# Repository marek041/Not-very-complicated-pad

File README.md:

# Not-very-complicated-pad
simple macro pad. 6 keys with oled display and Xiao RP2040. Macro pad for simple tasks like ctrl+c, ctrl+v, etc. also programs opening with windows search and shutdown button :O

## Features: 
- 6 keys
- 128x32 oled display
- 3 leds
- pretty silkcreen art
- cool case :)

## Cad design:
  This includes 3d printed case of 3 parts, everything is connected with M3 bolts screwed in plastic.
  
  It was made in Fusion360 and components imported from KiCad
  (i added step files so it could generate full PCB with components )

  it is all in cad folder

## PCB:
PCB i made in KiCad 

and Schematic 

## BOM:
  All components right there:

   - 6x Cheery MX switches
   - 6x DSA keycaps
   - 4x M3x16mm SHCS bolts
   - 6x 1N4148 DO-35 diodes
   - 3x WS28128 LEDs
   - 1x 0.91" 128x32 OLED Display
   - 1x XIAO RP2040
   - Case (3 printed parts)
 
## EXTRA stuff
This is my first project on Hack Club and also first time designing PCB
:D

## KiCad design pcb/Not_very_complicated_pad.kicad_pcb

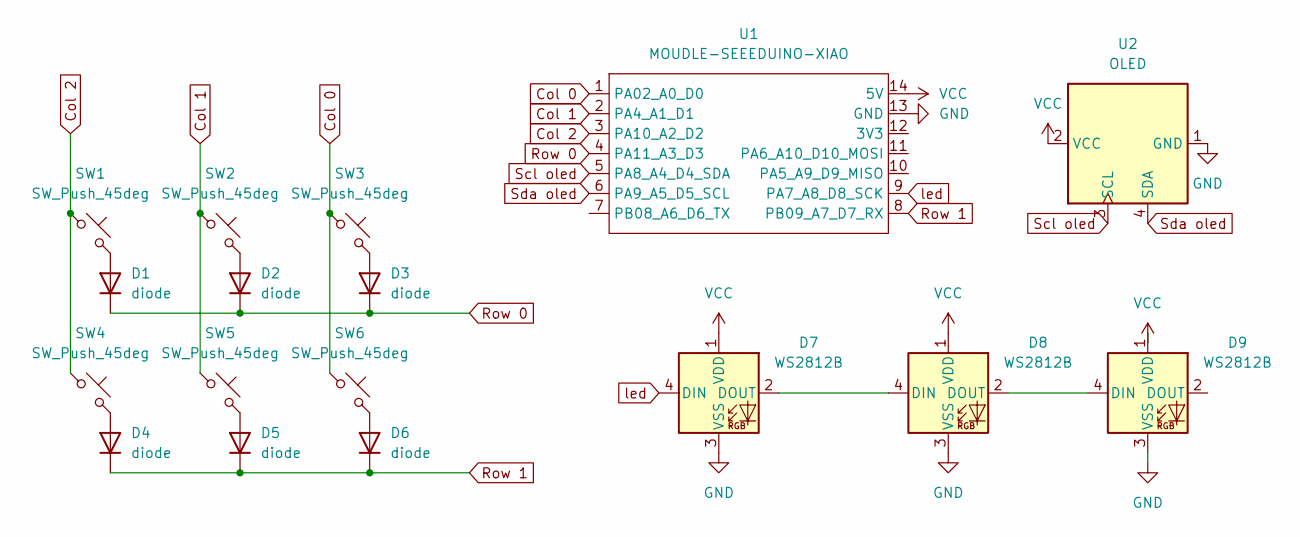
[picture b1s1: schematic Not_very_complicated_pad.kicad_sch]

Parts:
D1, D2, D3, D4, D5, D6: diode; D_DO-35_SOD27_P7.62mm_Horizontal
D7, D8, D9: WS2812B; LED_WS2812B_PLCC4_5.0x5.0mm_P3.2mm
SW1, SW2, SW3, SW4, SW5, SW6: SW_Push_45deg; SW_Cherry_MX_1.00u_PCB
U1: MOUDLE-SEEEDUINO-XIAO; XIAO-Generic-Hybrid-14P-2.54-21X17.8MM
U2: OLED; SSD1306-0.91-OLED-4pin-128x32

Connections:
Col 0: SW3.1, SW6.1, U1.1 (PA02_A0_D0)
Col 1: SW2.1, SW5.1, U1.2 (PA4_A1_D1)
Col 2: SW1.1, SW4.1, U1.3 (PA10_A2_D2)
GND: D7.3 (VSS), D8.3 (VSS), D9.3 (VSS), U1.13 (GND), U2.1 (GND)
unnamed: D1.2 (A), SW1.2
unnamed: D2.2 (A), SW2.2
unnamed: D3.2 (A), SW3.2
unnamed: D4.2 (A), SW4.2
unnamed: D5.2 (A), SW5.2
unnamed: D6.2 (A), SW6.2
unnamed: D7.2 (DOUT), D8.4 (DIN)
unnamed: D8.2 (DOUT), D9.4 (DIN)
Row 0: D1.1 (K), D2.1 (K), D3.1 (K), U1.4 (PA11_A3_D3)
Row 1: D4.1 (K), D5.1 (K), D6.1 (K), U1.8 (PB09_A7_D7_RX)
Scl oled: U1.5 (PA8_A4_D4_SDA), U2.3 (SCL)
Sda oled: U1.6 (PA9_A5_D5_SCL), U2.4 (SDA)
VCC: D7.1 (VDD), D8.1 (VDD), D9.1 (VDD), U1.14 (5V), U2.2 (VCC)
led: D7.4 (DIN), U1.9 (PA7_A8_D8_SCK)

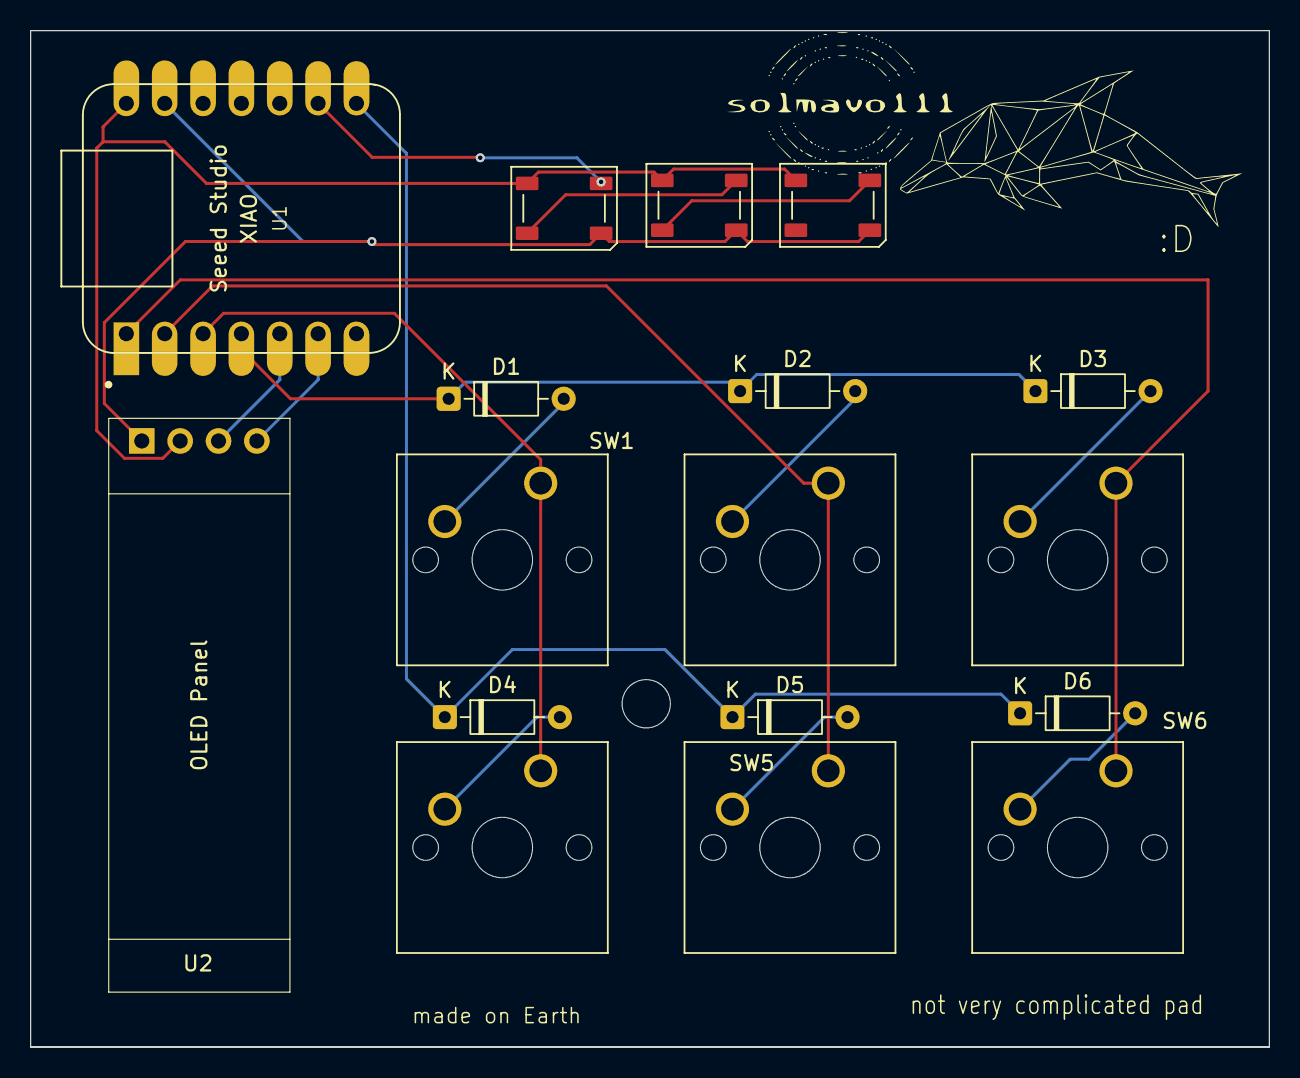
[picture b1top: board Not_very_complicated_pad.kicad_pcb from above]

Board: 2 copper layers, 82.0 x 67.3 mm, 17 parts (0 on the bottom side), 18 nets.
